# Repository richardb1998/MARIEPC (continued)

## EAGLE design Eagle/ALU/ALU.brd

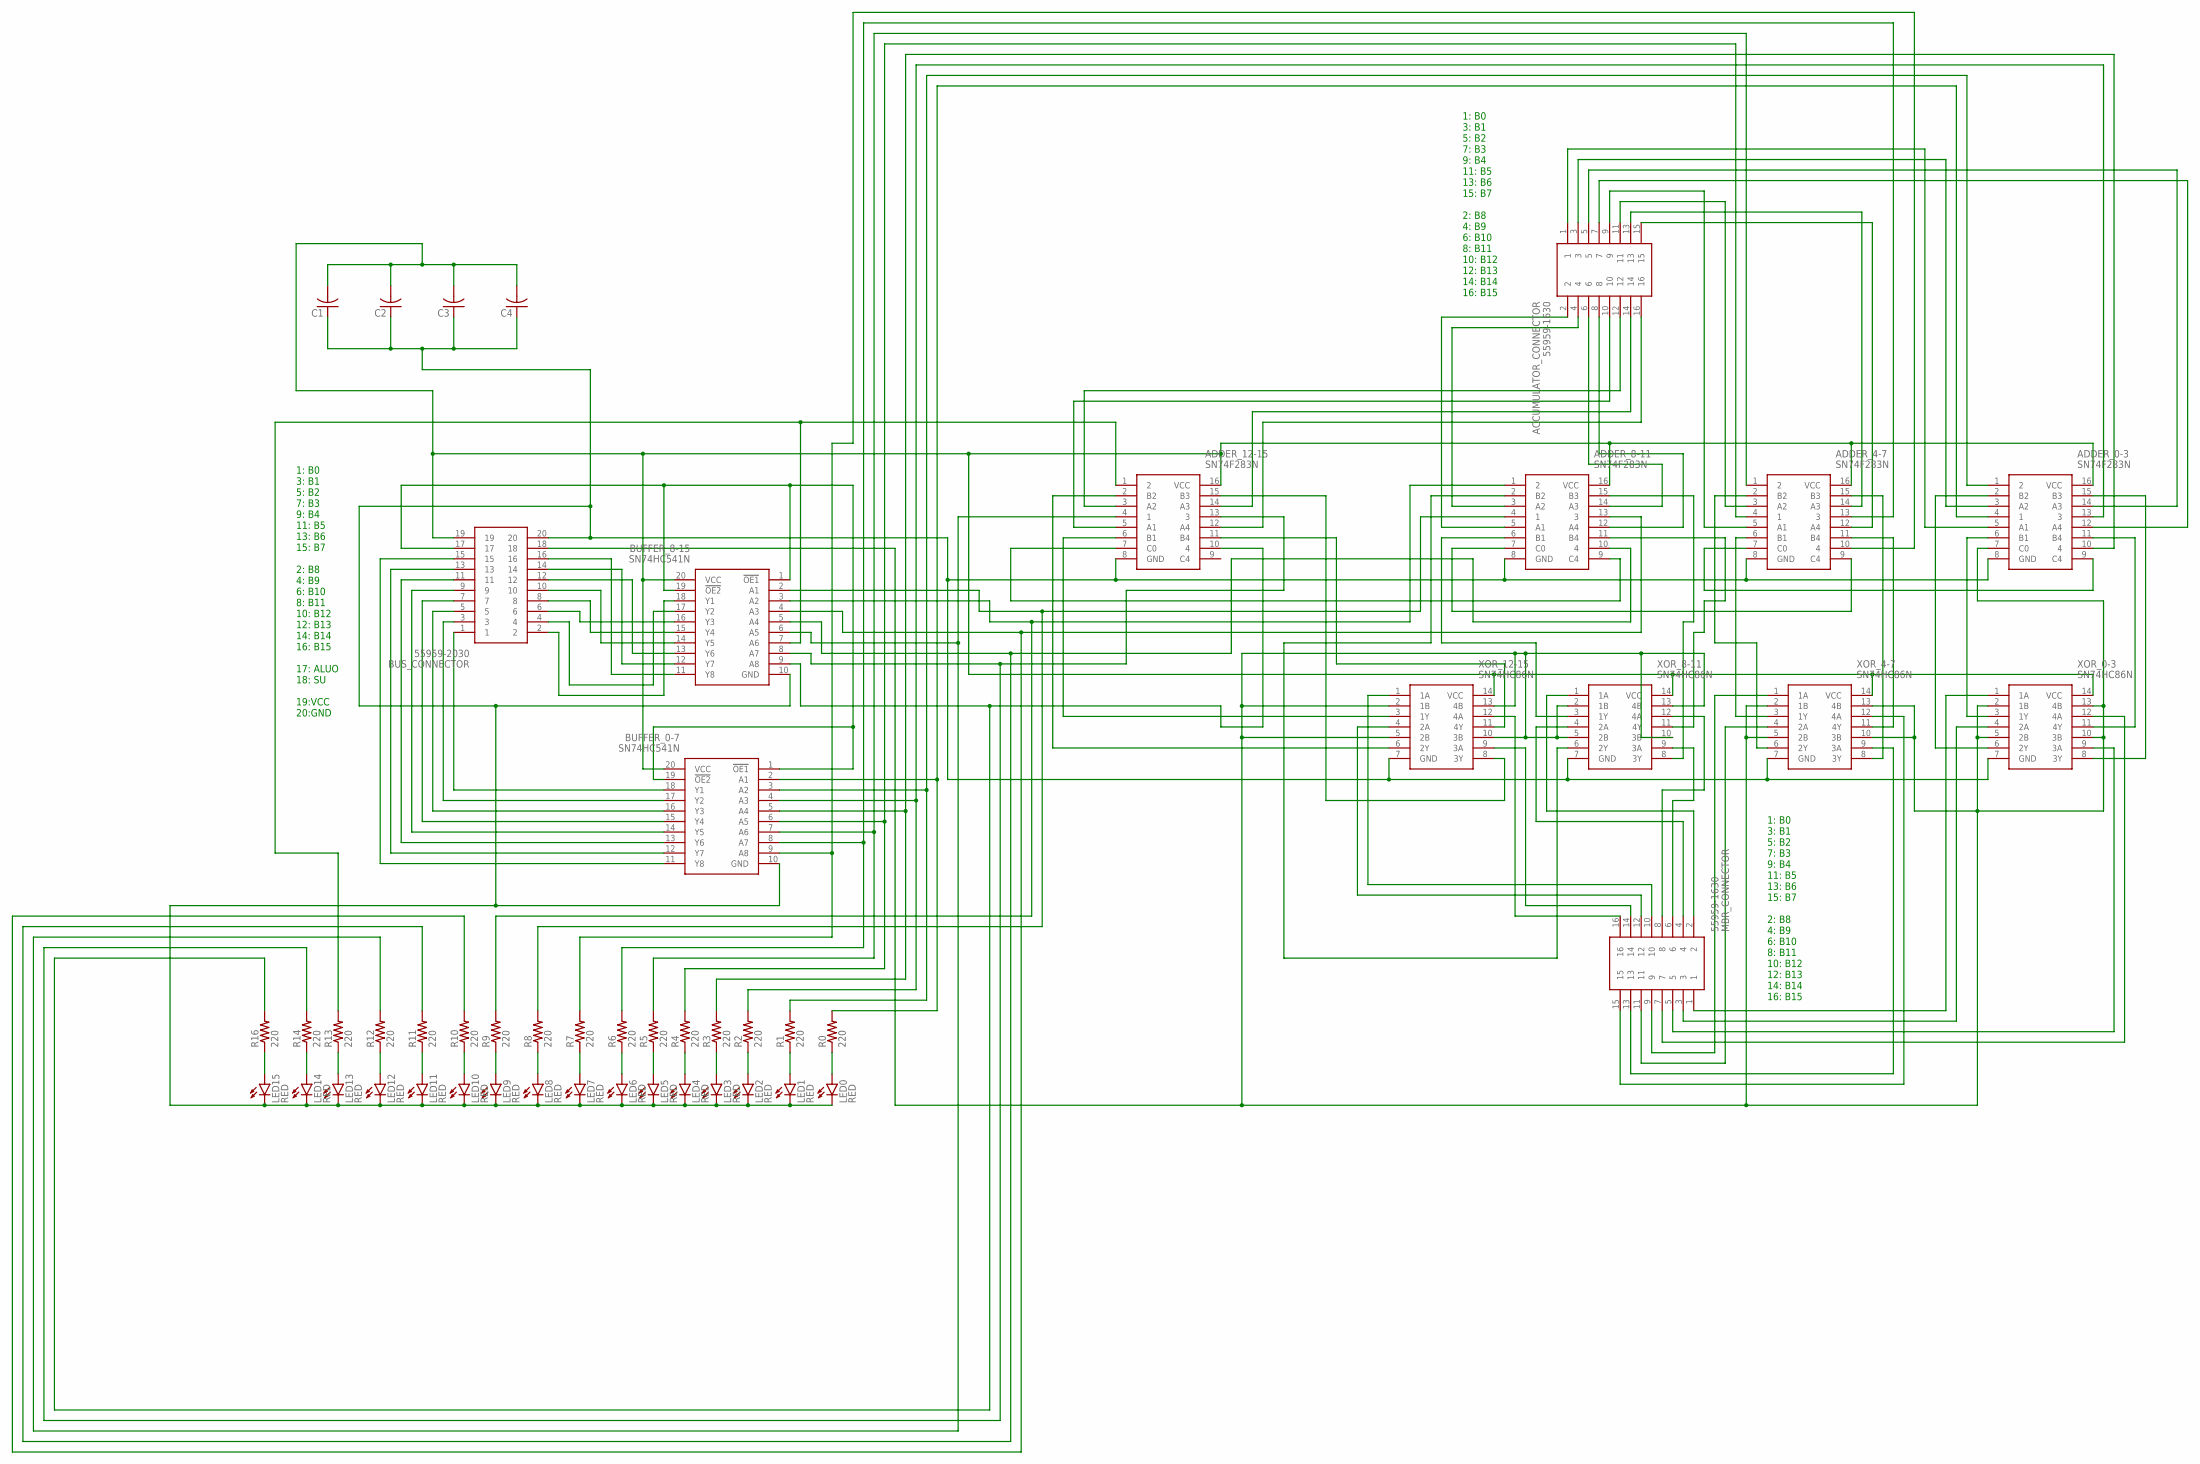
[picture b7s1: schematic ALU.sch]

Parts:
ACCUMULATOR_CONNECTOR: 55959-1630; SHDR16W65P250X200_2X8_1940X140
ADDER_0-3, ADDER_4-7, ADDER_8-11, ADDER_12-15: SN74F283N; DIP254P762X508-16
BUFFER_0-7, BUFFER_8-15: SN74HC541N; DIP794W53P254L2540H508Q20N
BUS_CONNECTOR: 55959-2030; 55959-2030_1
C1, C2, C3, C4: C-US025-024X044; C025-024X044
LED0, LED1, LED2, LED3, LED4, LED5, LED6, LED7, LED8, LED9, LED10, LED11, LED12, LED13, LED14, LED15: RED; LED3MM
MBR_CONNECTOR: 55959-1630; SHDR16W65P250X200_2X8_1940X140
R0, R1, R2, R3, R4, R5, R6, R7, R8, R9, R10, R11, R12, R13, R14, R16: 220; 0204/7
XOR_0-3, XOR_4-7, XOR_8-11, XOR_12-15: SN74HC86N; DIP794W53P254L1930H508Q14N

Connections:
unnamed: MBR_CONNECTOR.1, XOR_0-3.1 (1A)
unnamed: MBR_CONNECTOR.3, XOR_0-3.4 (2A)
unnamed: MBR_CONNECTOR.5, XOR_0-3.9 (3A)
unnamed: MBR_CONNECTOR.7, XOR_0-3.12 (4A)
unnamed: MBR_CONNECTOR.9, XOR_4-7.1 (1A)
unnamed: MBR_CONNECTOR.11, XOR_4-7.4 (2A)
unnamed: MBR_CONNECTOR.13, XOR_4-7.9 (3A)
unnamed: MBR_CONNECTOR.15, XOR_4-7.12 (4A)
unnamed: ADDER_0-3.6 (B1), XOR_0-3.3 (1Y)
unnamed: ADDER_0-3.2 (B2), XOR_0-3.6 (2Y)
unnamed: ADDER_0-3.15 (B3), XOR_0-3.8 (3Y)
unnamed: ADDER_0-3.11 (B4), XOR_0-3.11 (4Y)
unnamed: MBR_CONNECTOR.16, XOR_12-15.12 (4A)
unnamed: MBR_CONNECTOR.14, XOR_12-15.9 (3A)
unnamed: MBR_CONNECTOR.12, XOR_12-15.4 (2A)
unnamed: MBR_CONNECTOR.10, XOR_12-15.1 (1A)
unnamed: ADDER_4-7.9 (C4), ADDER_8-11.7 (C0)
unnamed: ADDER_8-11.9 (C4), ADDER_12-15.7 (C0)
unnamed: ADDER_0-3.9 (C4), ADDER_4-7.7 (C0)
unnamed: MBR_CONNECTOR.8, XOR_8-11.12 (4A)
unnamed: MBR_CONNECTOR.6, XOR_8-11.9 (3A)
unnamed: MBR_CONNECTOR.4, XOR_8-11.4 (2A)
unnamed: MBR_CONNECTOR.2, XOR_8-11.1 (1A)
unnamed: ADDER_4-7.6 (B1), XOR_4-7.3 (1Y)
unnamed: ADDER_4-7.2 (B2), XOR_4-7.6 (2Y)
unnamed: ADDER_4-7.15 (B3), XOR_4-7.8 (3Y)
unnamed: ADDER_4-7.11 (B4), XOR_4-7.11 (4Y)
unnamed: ACCUMULATOR_CONNECTOR.2, ADDER_8-11.5 (A1)
unnamed: ADDER_8-11.2 (B2), XOR_8-11.6 (2Y)
unnamed: ADDER_8-11.15 (B3), XOR_8-11.8 (3Y)
unnamed: ADDER_8-11.11 (B4), XOR_8-11.11 (4Y)
unnamed: ACCUMULATOR_CONNECTOR.15, ADDER_4-7.12 (A4)
unnamed: ACCUMULATOR_CONNECTOR.13, ADDER_4-7.14 (A3)
unnamed: ACCUMULATOR_CONNECTOR.11, ADDER_4-7.3 (A2)
unnamed: ACCUMULATOR_CONNECTOR.9, ADDER_4-7.5 (A1)
unnamed: ACCUMULATOR_CONNECTOR.7, ADDER_0-3.12 (A4)
unnamed: ACCUMULATOR_CONNECTOR.5, ADDER_0-3.14 (A3)
unnamed: ACCUMULATOR_CONNECTOR.3, ADDER_0-3.3 (A2)
unnamed: ACCUMULATOR_CONNECTOR.1, ADDER_0-3.5 (A1)
unnamed: ADDER_8-11.6 (B1), XOR_8-11.3 (1Y)
unnamed: ACCUMULATOR_CONNECTOR.4, ADDER_8-11.3 (A2)
unnamed: ACCUMULATOR_CONNECTOR.6, ADDER_8-11.14 (A3)
unnamed: ACCUMULATOR_CONNECTOR.8, ADDER_8-11.12 (A4)
unnamed: ACCUMULATOR_CONNECTOR.10, ADDER_12-15.5 (A1)
unnamed: ACCUMULATOR_CONNECTOR.12, ADDER_12-15.3 (A2)
unnamed: ACCUMULATOR_CONNECTOR.14, ADDER_12-15.14 (A3)
unnamed: ACCUMULATOR_CONNECTOR.16, ADDER_12-15.12 (A4)
unnamed: ADDER_12-15.2 (B2), XOR_12-15.6 (2Y)
unnamed: ADDER_12-15.6 (B1), XOR_12-15.3 (1Y)
unnamed: ADDER_12-15.15 (B3), XOR_12-15.8 (3Y)
unnamed: ADDER_12-15.11 (B4), XOR_12-15.11 (4Y)
unnamed: ADDER_0-3.8 (GND), ADDER_4-7.8 (GND), ADDER_8-11.8 (GND), ADDER_12-15.8 (GND), BUFFER_0-7.10 (GND), BUFFER_8-15.10 (GND), BUS_CONNECTOR.20, C1.1, C2.1, C3.1, C4.1, LED0.K (C), LED1.K (C), LED2.K (C), LED3.K (C), LED4.K (C), LED5.K (C), LED6.K (C), LED7.K (C), LED8.K (C), LED9.K (C), LED10.K (C), LED11.K (C), LED12.K (C), LED13.K (C), LED14.K (C), LED15.K (C), XOR_0-3.7 (GND), XOR_4-7.7 (GND), XOR_8-11.7 (GND), XOR_12-15.7 (GND)
unnamed: BUFFER_0-7.18 (Y1), BUS_CONNECTOR.1
unnamed: ADDER_0-3.16 (VCC), ADDER_4-7.16 (VCC), ADDER_8-11.16 (VCC), ADDER_12-15.16 (VCC), BUFFER_0-7.20 (VCC), BUFFER_8-15.20 (VCC), BUS_CONNECTOR.19, C1.2, C2.2, C3.2, C4.2, XOR_0-3.14 (VCC), XOR_4-7.14 (VCC), XOR_8-11.14 (VCC), XOR_12-15.14 (VCC)
unnamed: BUFFER_0-7.17 (Y2), BUS_CONNECTOR.3
unnamed: BUFFER_0-7.16 (Y3), BUS_CONNECTOR.5
unnamed: BUFFER_0-7.15 (Y4), BUS_CONNECTOR.7
unnamed: BUFFER_0-7.14 (Y5), BUS_CONNECTOR.9
unnamed: BUFFER_0-7.13 (Y6), BUS_CONNECTOR.11
unnamed: BUFFER_0-7.12 (Y7), BUS_CONNECTOR.13
unnamed: BUFFER_0-7.11 (Y8), BUS_CONNECTOR.15
unnamed: BUFFER_8-15.15 (Y4), BUS_CONNECTOR.8
unnamed: BUFFER_8-15.16 (Y3), BUS_CONNECTOR.6
unnamed: BUFFER_8-15.11 (Y8), BUS_CONNECTOR.16
unnamed: BUFFER_8-15.12 (Y7), BUS_CONNECTOR.14
unnamed: BUFFER_8-15.13 (Y6), BUS_CONNECTOR.12
unnamed: BUFFER_8-15.14 (Y5), BUS_CONNECTOR.10
unnamed: BUFFER_8-15.17 (Y2), BUS_CONNECTOR.4
unnamed: BUFFER_8-15.18 (Y1), BUS_CONNECTOR.2
unnamed: BUFFER_0-7.1 (!OE1), BUFFER_0-7.19 (!OE2), BUFFER_8-15.1 (!OE1), BUFFER_8-15.19 (!OE2), BUS_CONNECTOR.17
unnamed: ADDER_0-3.4 (1), BUFFER_0-7.2 (A1), R0.2
unnamed: ADDER_0-3.7 (C0), BUS_CONNECTOR.18, XOR_0-3.2 (1B), XOR_0-3.5 (2B), XOR_0-3.10 (3B), XOR_0-3.13 (4B), XOR_4-7.2 (1B), XOR_4-7.5 (2B), XOR_4-7.10 (3B), XOR_4-7.13 (4B), XOR_8-11.2 (1B), XOR_8-11.5 (2B), XOR_8-11.10 (3B), XOR_8-11.13 (4B), XOR_12-15.2 (1B), XOR_12-15.5 (2B), XOR_12-15.10 (3B), XOR_12-15.13 (4B)
unnamed: ADDER_0-3.1 (2), BUFFER_0-7.3 (A2), R1.2
unnamed: ADDER_0-3.13 (3), BUFFER_0-7.4 (A3), R2.2
unnamed: ADDER_0-3.10 (4), BUFFER_0-7.5 (A4), R3.2
unnamed: ADDER_4-7.4 (1), BUFFER_0-7.6 (A5), R4.2
unnamed: ADDER_4-7.1 (2), BUFFER_0-7.7 (A6), R5.2
unnamed: ADDER_4-7.13 (3), BUFFER_0-7.8 (A7), R6.2
unnamed: ADDER_4-7.10 (4), BUFFER_0-7.9 (A8), R7.2
unnamed: ADDER_8-11.4 (1), BUFFER_8-15.2 (A1), R8.2
unnamed: ADDER_8-11.1 (2), BUFFER_8-15.3 (A2), R9.2
unnamed: ADDER_8-11.13 (3), BUFFER_8-15.4 (A3), R10.2
unnamed: ADDER_8-11.10 (4), BUFFER_8-15.5 (A4), R11.2
unnamed: ADDER_12-15.4 (1), BUFFER_8-15.6 (A5), R12.2
unnamed: ADDER_12-15.1 (2), BUFFER_8-15.7 (A6), R13.2
unnamed: ADDER_12-15.10 (4), BUFFER_8-15.9 (A8), R16.2
unnamed: LED15.A, R16.1
unnamed: ADDER_12-15.13 (3), BUFFER_8-15.8 (A7), R14.2
unnamed: LED14.A, R14.1
unnamed: LED13.A, R13.1
unnamed: LED12.A, R12.1
unnamed: LED11.A, R11.1
unnamed: LED10.A, R10.1
unnamed: LED9.A, R9.1
unnamed: LED8.A, R8.1
unnamed: LED7.A, R7.1
unnamed: LED6.A, R6.1
unnamed: LED5.A, R5.1
unnamed: LED4.A, R4.1
unnamed: LED3.A, R3.1
unnamed: LED2.A, R2.1
unnamed: LED1.A, R1.1
unnamed: LED0.A, R0.1

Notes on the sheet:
1: B0 3: B1 5: B2 7: B3 9: B4 11: B5 13: B6 15: B7 2: B8 4: B9 6: B10 8: B11 10: B12 12: B13 14: B14 16: B15 17: ALUO 18: SU 19:VCC 20:GND
1: B0 3: B1 5: B2 7: B3 9: B4 11: B5 13: B6 15: B7 2: B8 4: B9 6: B10 8: B11 10: B12 12: B13 14: B14 16: B15

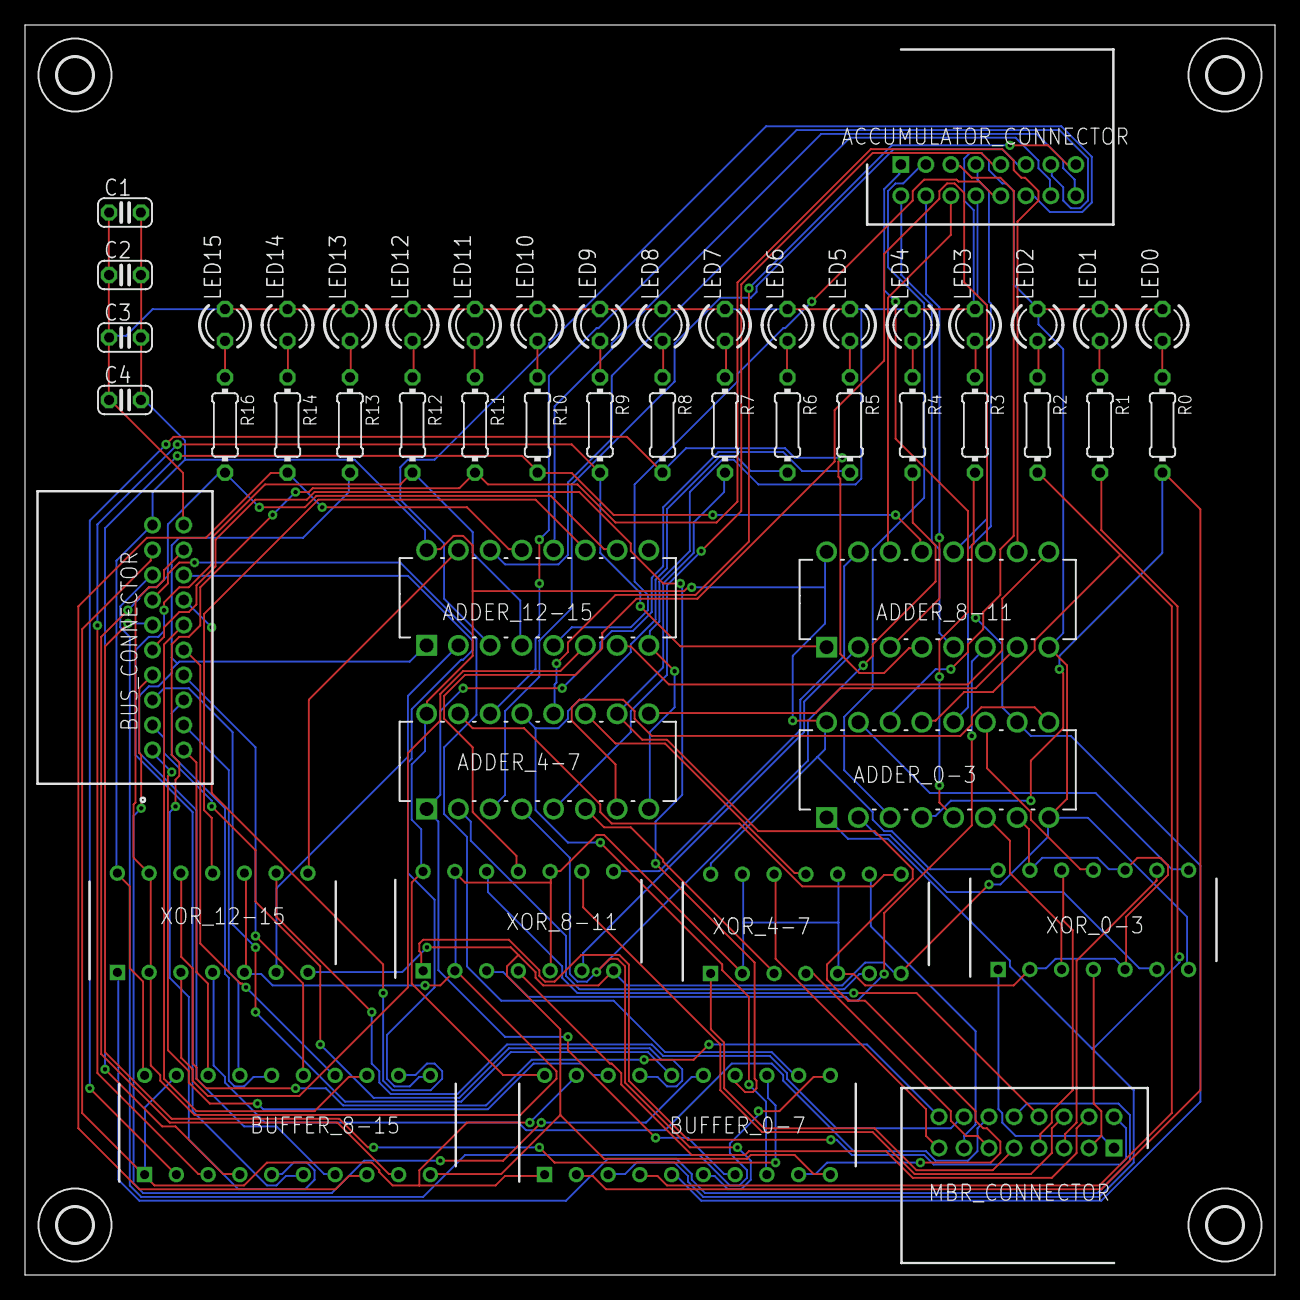
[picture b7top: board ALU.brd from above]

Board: 2 copper layers, 100.0 x 100.0 mm, 53 parts (0 on the bottom side), 103 nets.

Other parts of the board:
U$1, U$2, U$3, U$4: 2,8

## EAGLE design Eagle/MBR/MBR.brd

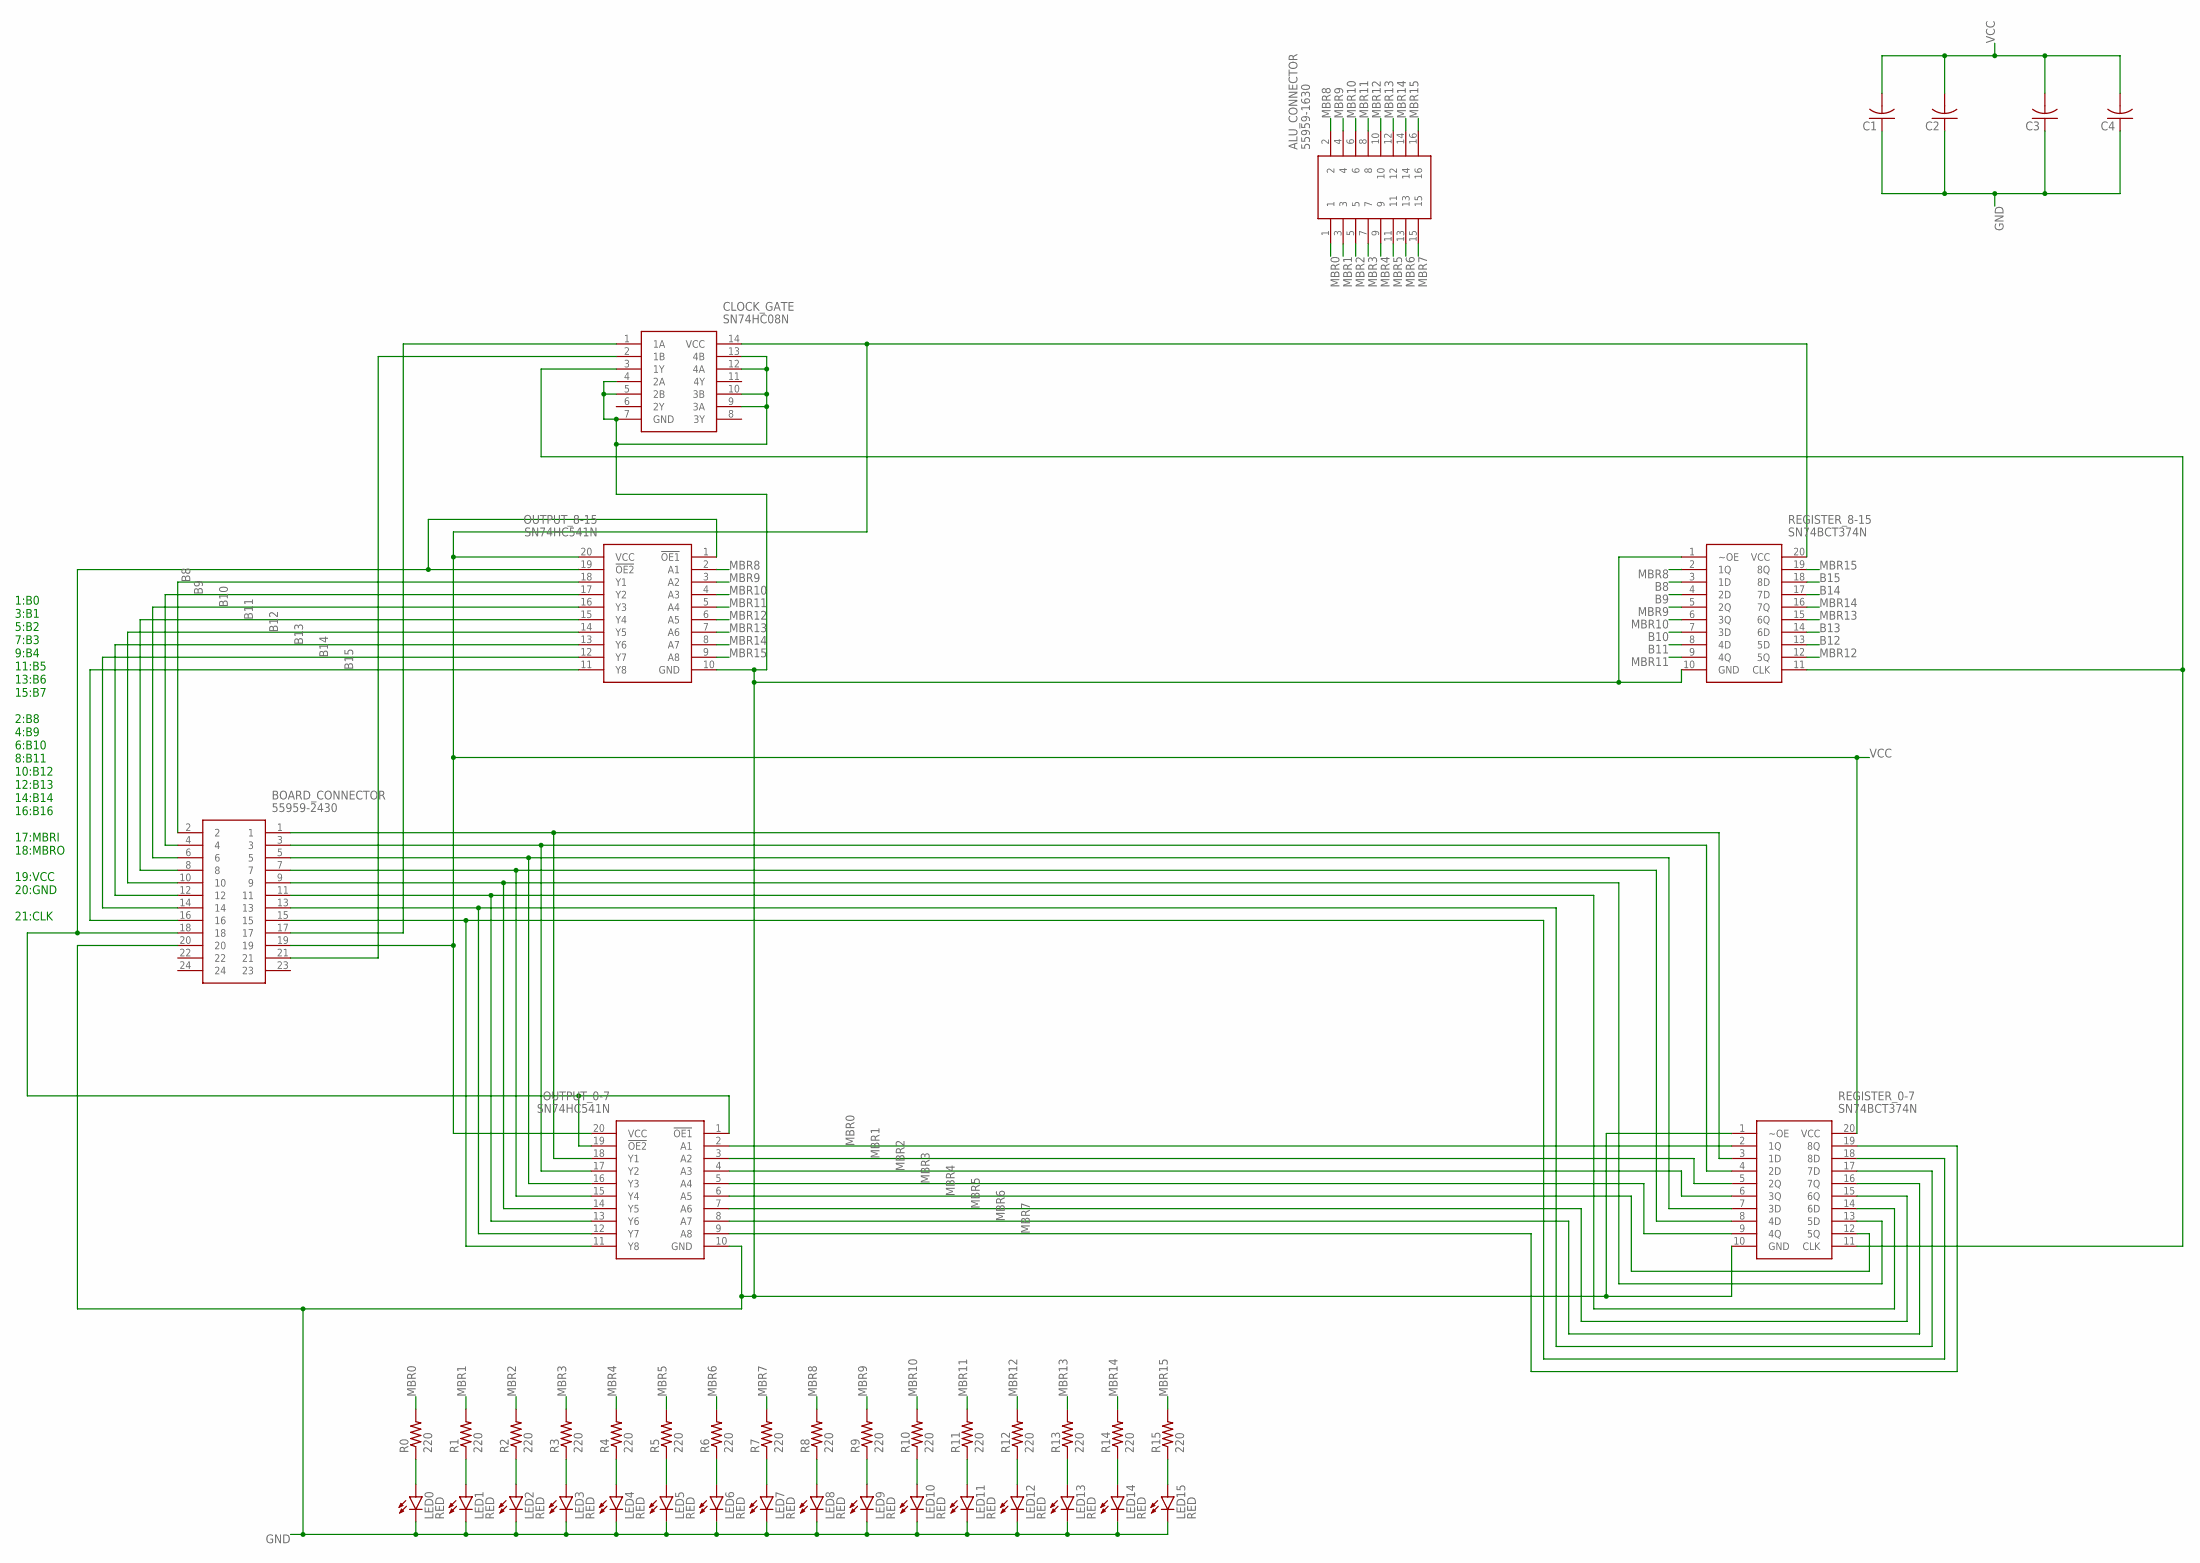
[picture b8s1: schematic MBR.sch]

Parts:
ALU_CONNECTOR: 55959-1630; SHDR16W65P250X200_2X8_1940X140
BOARD_CONNECTOR: 55959-2430; 559592430
C1, C2, C3, C4: C-US025-024X044; C025-024X044
CLOCK_GATE: SN74HC08N; DIP794W53P254L1930H508Q14N
LED0, LED1, LED2, LED3, LED4, LED5, LED6, LED7, LED8, LED9, LED10, LED11, LED12, LED13, LED14, LED15: RED; LED3MM
OUTPUT_0-7, OUTPUT_8-15: SN74HC541N; DIP794W53P254L2540H508Q20N
R0, R1, R2, R3, R4, R5, R6, R7, R8, R9, R10, R11, R12, R13, R14, R15: 220; 0204/7
REGISTER_0-7, REGISTER_8-15: SN74BCT374N; DIP254P762X508-20

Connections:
B8: BOARD_CONNECTOR.2, OUTPUT_8-15.18 (Y1), REGISTER_8-15.3 (1D)
B9: BOARD_CONNECTOR.4, OUTPUT_8-15.17 (Y2), REGISTER_8-15.4 (2D)
B10: BOARD_CONNECTOR.6, OUTPUT_8-15.16 (Y3), REGISTER_8-15.7 (3D)
B11: BOARD_CONNECTOR.8, OUTPUT_8-15.15 (Y4), REGISTER_8-15.8 (4D)
B12: BOARD_CONNECTOR.10, OUTPUT_8-15.14 (Y5), REGISTER_8-15.13 (5D)
B13: BOARD_CONNECTOR.12, OUTPUT_8-15.13 (Y6), REGISTER_8-15.14 (6D)
B14: BOARD_CONNECTOR.14, OUTPUT_8-15.12 (Y7), REGISTER_8-15.17 (7D)
B15: BOARD_CONNECTOR.16, OUTPUT_8-15.11 (Y8), REGISTER_8-15.18 (8D)
GND: BOARD_CONNECTOR.20, C1.1, C2.1, C3.1, C4.1, CLOCK_GATE.4 (2A), CLOCK_GATE.5 (2B), CLOCK_GATE.7 (GND), CLOCK_GATE.9 (3A), CLOCK_GATE.10 (3B), CLOCK_GATE.12 (4A), CLOCK_GATE.13 (4B), LED0.K (C), LED1.K (C), LED2.K (C), LED3.K (C), LED4.K (C), LED5.K (C), LED6.K (C), LED7.K (C), LED8.K (C), LED9.K (C), LED10.K (C), LED11.K (C), LED12.K (C), LED13.K (C), LED14.K (C), LED15.K (C), OUTPUT_0-7.10 (GND), OUTPUT_8-15.10 (GND), REGISTER_0-7.1 (~OE), REGISTER_0-7.10 (GND), REGISTER_8-15.1 (~OE), REGISTER_8-15.10 (GND)
MBR0: ALU_CONNECTOR.1, OUTPUT_0-7.2 (A1), R0.2, REGISTER_0-7.2 (1Q)
MBR1: ALU_CONNECTOR.3, OUTPUT_0-7.3 (A2), R1.2, REGISTER_0-7.5 (2Q)
MBR2: ALU_CONNECTOR.5, OUTPUT_0-7.4 (A3), R2.2, REGISTER_0-7.6 (3Q)
MBR3: ALU_CONNECTOR.7, OUTPUT_0-7.5 (A4), R3.2, REGISTER_0-7.9 (4Q)
MBR4: ALU_CONNECTOR.9, OUTPUT_0-7.6 (A5), R4.2, REGISTER_0-7.12 (5Q)
MBR5: ALU_CONNECTOR.11, OUTPUT_0-7.7 (A6), R5.2, REGISTER_0-7.15 (6Q)
MBR6: ALU_CONNECTOR.13, OUTPUT_0-7.8 (A7), R6.2, REGISTER_0-7.16 (7Q)
MBR7: ALU_CONNECTOR.15, OUTPUT_0-7.9 (A8), R7.2, REGISTER_0-7.19 (8Q)
MBR8: ALU_CONNECTOR.2, OUTPUT_8-15.2 (A1), R8.2, REGISTER_8-15.2 (1Q)
MBR9: ALU_CONNECTOR.4, OUTPUT_8-15.3 (A2), R9.2, REGISTER_8-15.5 (2Q)
MBR10: ALU_CONNECTOR.6, OUTPUT_8-15.4 (A3), R10.2, REGISTER_8-15.6 (3Q)
MBR11: ALU_CONNECTOR.8, OUTPUT_8-15.5 (A4), R11.2, REGISTER_8-15.9 (4Q)
MBR12: ALU_CONNECTOR.10, OUTPUT_8-15.6 (A5), R12.2, REGISTER_8-15.12 (5Q)
MBR13: ALU_CONNECTOR.12, OUTPUT_8-15.7 (A6), R13.2, REGISTER_8-15.15 (6Q)
MBR14: ALU_CONNECTOR.14, OUTPUT_8-15.8 (A7), R14.2, REGISTER_8-15.16 (7Q)
MBR15: ALU_CONNECTOR.16, OUTPUT_8-15.9 (A8), R15.2, REGISTER_8-15.19 (8Q)
unnamed: BOARD_CONNECTOR.15, OUTPUT_0-7.11 (Y8), REGISTER_0-7.18 (8D)
unnamed: BOARD_CONNECTOR.13, OUTPUT_0-7.12 (Y7), REGISTER_0-7.17 (7D)
unnamed: BOARD_CONNECTOR.11, OUTPUT_0-7.13 (Y6), REGISTER_0-7.14 (6D)
unnamed: BOARD_CONNECTOR.9, OUTPUT_0-7.14 (Y5), REGISTER_0-7.13 (5D)
unnamed: BOARD_CONNECTOR.7, OUTPUT_0-7.15 (Y4), REGISTER_0-7.8 (4D)
unnamed: BOARD_CONNECTOR.5, OUTPUT_0-7.16 (Y3), REGISTER_0-7.7 (3D)
unnamed: BOARD_CONNECTOR.3, OUTPUT_0-7.17 (Y2), REGISTER_0-7.4 (2D)
unnamed: BOARD_CONNECTOR.1, OUTPUT_0-7.18 (Y1), REGISTER_0-7.3 (1D)
unnamed: LED0.A, R0.1
unnamed: LED1.A, R1.1
unnamed: LED2.A, R2.1
unnamed: LED3.A, R3.1
unnamed: LED4.A, R4.1
unnamed: LED5.A, R5.1
unnamed: LED6.A, R6.1
unnamed: LED7.A, R7.1
unnamed: BOARD_CONNECTOR.18, OUTPUT_0-7.1 (!OE1), OUTPUT_0-7.19 (!OE2), OUTPUT_8-15.1 (!OE1), OUTPUT_8-15.19 (!OE2)
unnamed: CLOCK_GATE.3 (1Y), REGISTER_0-7.11 (CLK), REGISTER_8-15.11 (CLK)
unnamed: LED8.A, R8.1
unnamed: BOARD_CONNECTOR.17, CLOCK_GATE.1 (1A)
unnamed: BOARD_CONNECTOR.21, CLOCK_GATE.2 (1B)
unnamed: LED9.A, R9.1
unnamed: LED10.A, R10.1
unnamed: LED11.A, R11.1
unnamed: LED12.A, R12.1
unnamed: LED13.A, R13.1
unnamed: LED14.A, R14.1
unnamed: LED15.A, R15.1
VCC: BOARD_CONNECTOR.19, C1.2, C2.2, C3.2, C4.2, CLOCK_GATE.14 (VCC), OUTPUT_0-7.20 (VCC), OUTPUT_8-15.20 (VCC), REGISTER_0-7.20 (VCC), REGISTER_8-15.20 (VCC)

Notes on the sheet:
1:B0 3:B1 5:B2 7:B3 9:B4 11:B5 13:B6 15:B7 2:B8 4:B9 6:B10 8:B11 10:B12 12:B13 14:B14 16:B16 17:MBRI 18:MBRO 19:VCC 20:GND 21:CLK

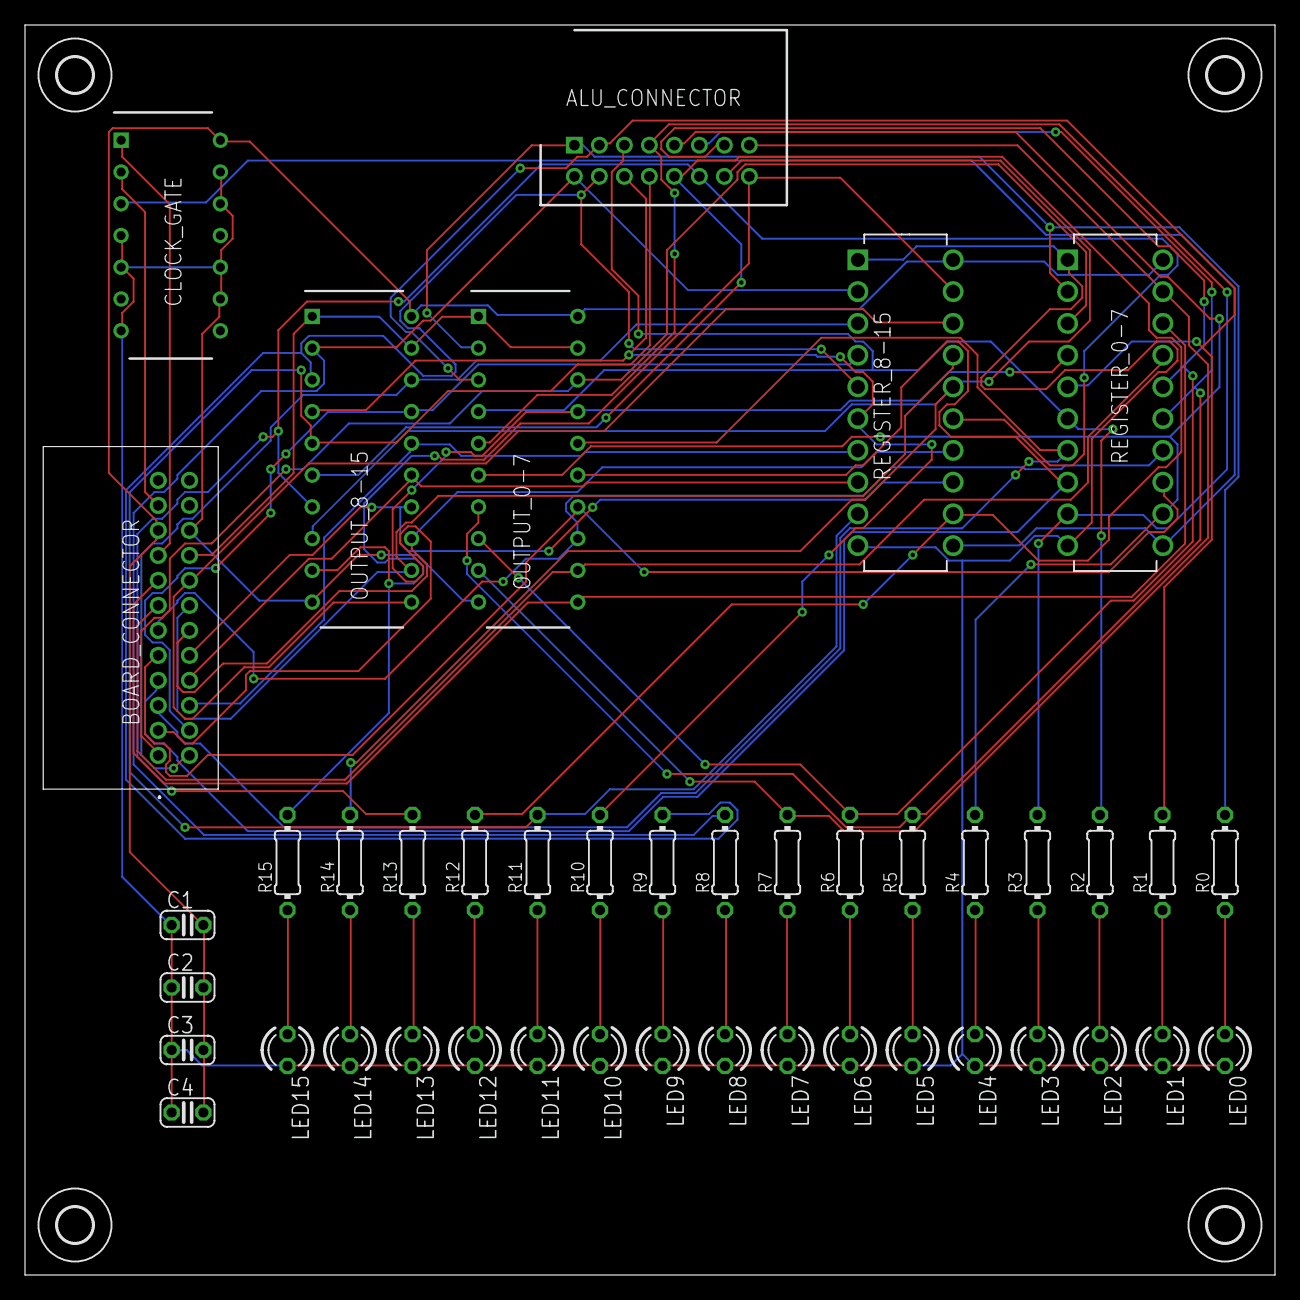
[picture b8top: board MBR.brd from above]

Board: 2 copper layers, 100.0 x 100.0 mm, 47 parts (0 on the bottom side), 54 nets.

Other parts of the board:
U$1, U$2, U$3, U$4: 2,8

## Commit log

2019-09-27 finished implementing Program Counter
2020-01-22 added logisim
2020-01-22 Added ALU schematic in Eagle
2020-01-25 Added MBR
2020-01-27 started implementation of Program Counter
2020-02-02 Added program counter
2020-02-03 started working on Memory
2020-02-05 almost finished memory
2020-02-10 fixed skipcond logic in logisim and added more registers to MARIE
2020-02-15 worked on accumulator
2020-02-17 Added input to logisim and worked on IR
2020-02-19 Worked on IR
2020-02-19 added parts needed to finish boards
2020-02-19 Finished IR
2020-02-19 added HLT to MAR for prgm mode
2020-02-21 finished most boards
2020-02-24 added Clock
2020-02-25 added BUS
2020-02-25 added pull down resistors and reset circuit to BUS
2020-02-25 added flyback diode
2020-02-25 added gerber files for each board
2020-02-25 added power connector
2020-02-25 added gerber files for ordering boards
2020-03-20 updating repo
2020-06-12 started adding revision 2 to fix errors in first set of boards
2020-06-26 updated schematics
